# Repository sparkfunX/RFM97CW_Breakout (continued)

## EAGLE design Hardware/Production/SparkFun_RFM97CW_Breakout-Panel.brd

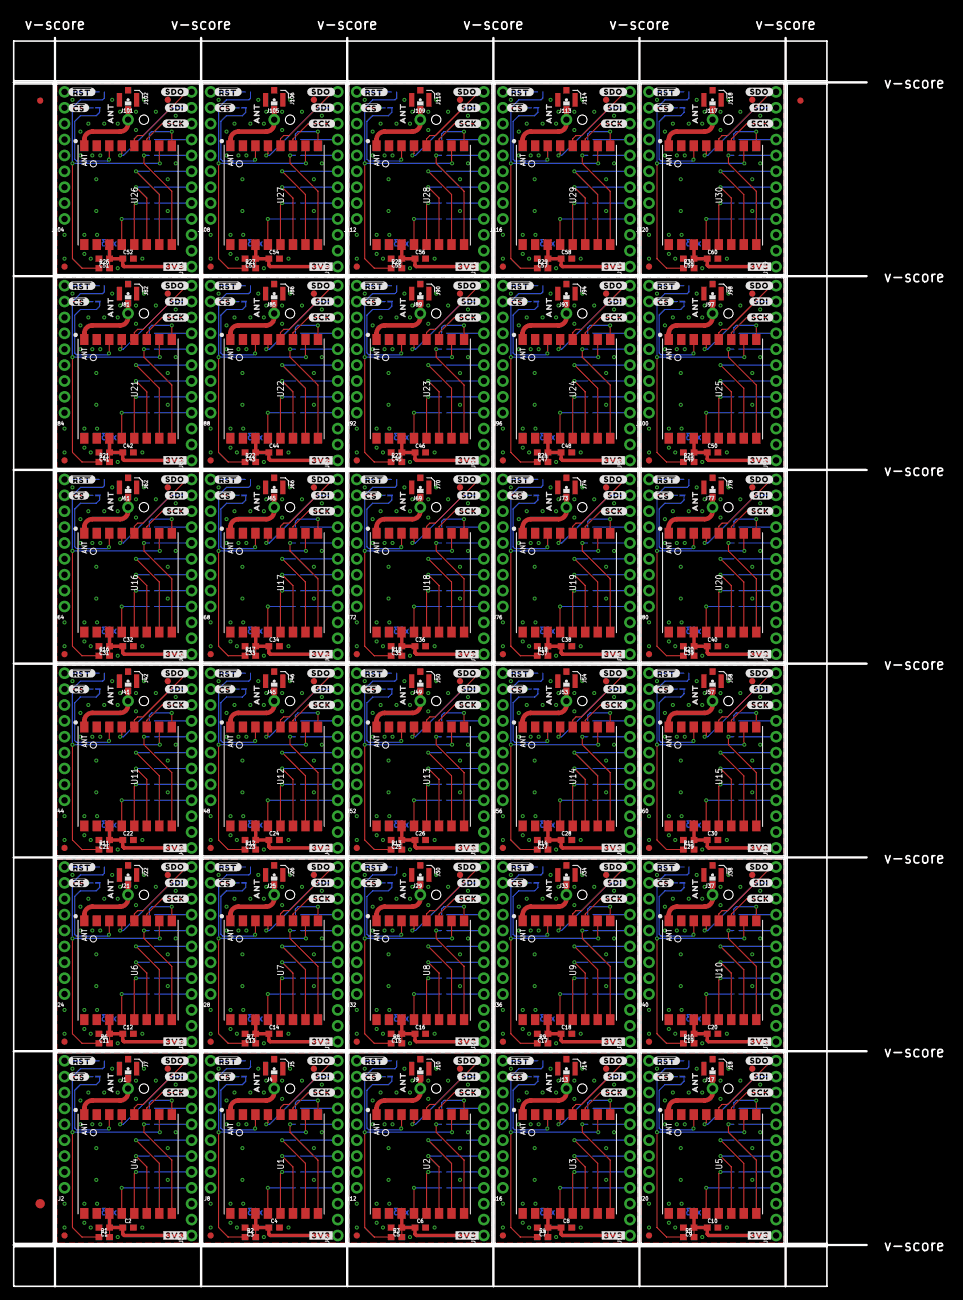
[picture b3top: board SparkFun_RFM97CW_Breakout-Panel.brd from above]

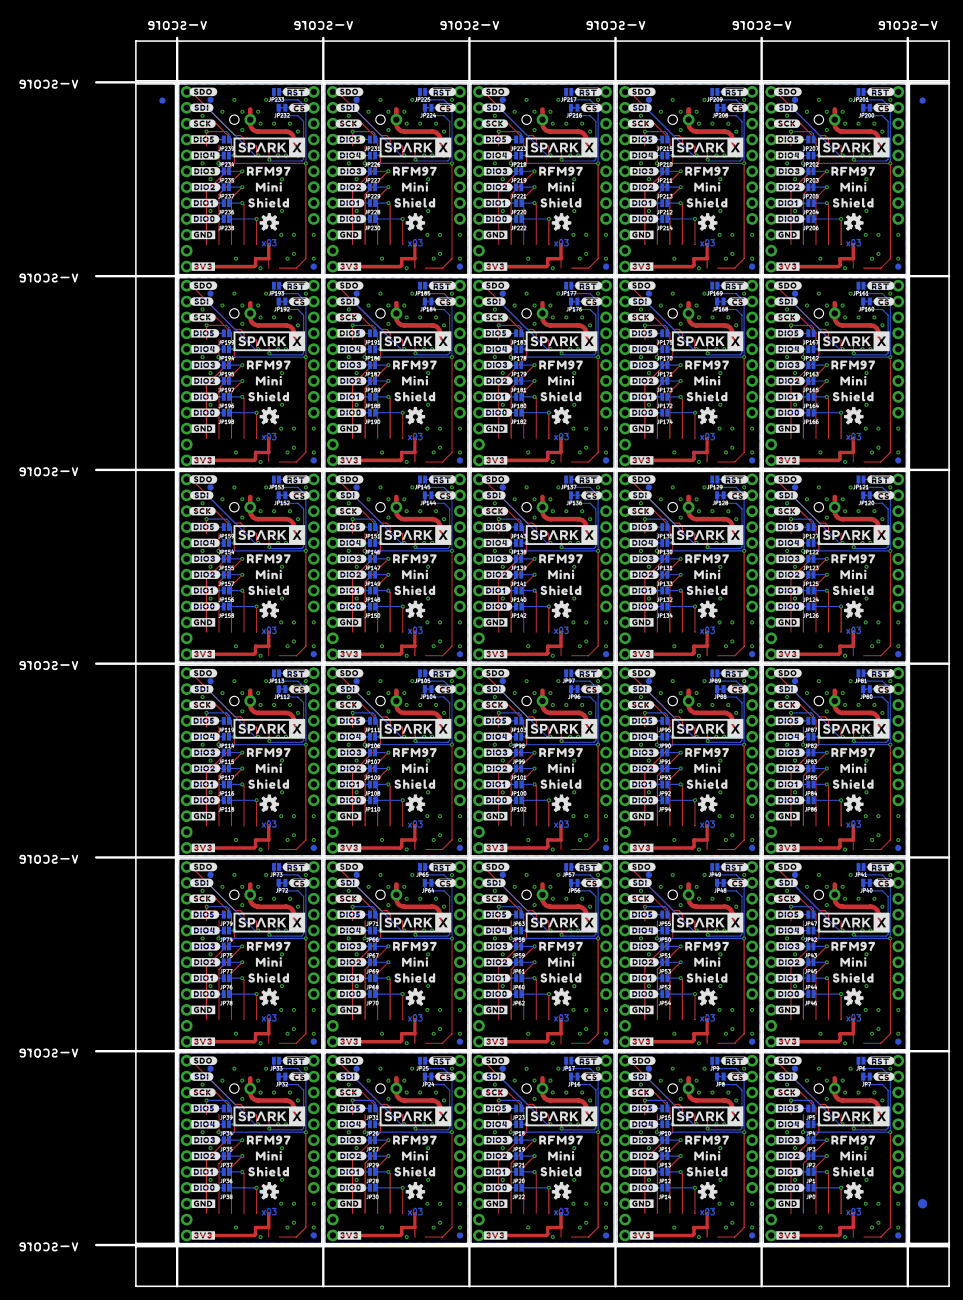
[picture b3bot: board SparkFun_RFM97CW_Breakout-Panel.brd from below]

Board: 2 copper layers, 149.6 x 203.5 mm, 1356 parts (843 on the bottom side), 660 nets.

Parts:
C1, C3, C5, C7, C9, C11, C13, C15, C17, C19, C21, C23, C25, C27, C29, C31, C33, C35, C37, C39, C41, C43, C45, C47, C49, C51, C53, C55, C57, C59: 10uF; 0603
C2, C4, C6, C8, C10, C12, C14, C16, C18, C20, C22, C24, C26, C28, C30, C32, C34, C36, C38, C40, C42, C44, C46, C48, C50, C52, C54, C56, C58, C60: 0.1uF; 0603
E$1, E$2, E$3, E$4: FIDUCIAL-1X2
E$5, E$6: FIDUCIAL-1.5X3
FID1, FID2, FID3, FID4, FID5, FID6, FID7, FID8, FID9, FID10, FID11, FID12, FID13, FID14, FID15, FID16, FID17, FID18, FID19, FID20, FID21, FID22, FID23, FID24, FID25, FID26, FID27, FID28, FID29, FID30, FID31, FID32, FID33, FID34, FID35, FID36, FID37, FID38, FID39, FID40, FID41, FID42, FID43, FID44, FID45, FID46, FID47, FID48, FID49, FID50, FID51, FID52, FID53, FID54, FID55, FID56, FID57, FID58, FID59, FID60, FID61, FID62, FID63, FID64, FID65, FID66, FID67, FID68, FID69, FID70, FID71, FID72, FID73, FID74, FID75, FID76, FID77, FID78, FID79, FID80, FID81, FID82, FID83, FID84, FID85, FID86, FID87, FID88, FID89, FID90, FID91, FID92, FID93, FID94, FID95, FID96, FID97, FID98, FID99, FID100, FID101, FID102, FID103, FID104, FID105, FID106, FID107, FID108, FID109, FID110, FID111, FID112, FID113, FID114, FID115, FID116, FID117, FID118, FID119, FID120: FIDUCIAL1X2; FIDUCIAL-1X2
J1, J4, J9, J13, J17, J21, J25, J29, J33, J37, J41, J45, J49, J53, J57, J61, J65, J69, J73, J77, J81, J85, J89, J93, J97, J101, J105, J109, J113, J117: 1X01_NO_SILK
J2, J8, J12, J16, J20, J24, J28, J32, J36, J40, J44, J48, J52, J56, J60, J64, J68, J72, J76, J80, J84, J88, J92, J96, J100, J104, J108, J112, J116, J120: 1X09_NO_SILK
J3, J6, J11, J15, J19, J23, J27, J31, J35, J39, J43, J47, J51, J55, J59, J63, J67, J71, J75, J79, J83, J87, J91, J95, J99, J103, J107, J111, J115, J119: 1X12_NO_SILK
J5, J7, J10, J14, J18, J22, J26, J30, J34, J38, J42, J46, J50, J54, J58, J62, J66, J70, J74, J78, J82, J86, J90, J94, J98, J102, J106, J110, J114, J118: U.FL
JP0, JP1, JP2, JP3, JP4, JP5, JP6, JP9, JP10, JP11, JP12, JP13, JP14, JP15, JP17, JP18, JP19, JP20, JP21, JP22, JP23, JP25, JP26, JP27, JP28, JP29, JP30, JP31, JP33, JP34, JP35, JP36, JP37, JP38, JP39, JP41, JP42, JP43, JP44, JP45, JP46, JP47, JP49, JP50, JP51, JP52, JP53, JP54, JP55, JP57, JP58, JP59, JP60, JP61, JP62, JP63, JP65, JP66, JP67, JP68, JP69, JP70, JP71, JP73, JP74, JP75, JP76, JP77, JP78, JP79, JP81, JP82, JP83, JP84, JP85, JP86, JP87, JP89, JP90, JP91, JP92, JP93, JP94, JP95, JP97, JP98, JP99, JP100, JP101, JP102, JP103, JP105, JP106, JP107, JP108, JP109, JP110, JP111, JP113, JP114, JP115, JP116, JP117, JP118, JP119, JP121, JP122, JP123, JP124, JP125, JP126, JP127, JP129, JP130, JP131, JP132, JP133, JP134, JP135, JP137, JP138, JP139, JP140, JP141, JP142, JP143, JP145, JP146, JP147, JP148, JP149, JP150, JP151, JP153, JP154, JP155, JP156, JP157, JP158, JP159, JP161, JP162, JP163, JP164, JP165, JP166, JP167, JP169, JP170, JP171, JP172, JP173, JP174, JP175, JP177, JP178, JP179, JP180, JP181, JP182, JP183, JP185, JP186, JP187, JP188, JP189, JP190, JP191, JP193, JP194, JP195, JP196, JP197, JP198, JP199, JP201, JP202, JP203, JP204, JP205, JP206, JP207, JP209, JP210, JP211, JP212, JP213, JP214, JP215, JP217, JP218, JP219, JP220, JP221, JP222, JP223, JP225, JP226, JP227, JP228, JP229, JP230, JP231, JP233, JP234, JP235, JP236, JP237, JP238, JP239: JUMPER-SMT_2_NO_NO-SILK; SMT-JUMPER_2_NO_NO-SILK
JP7, JP8, JP16, JP24, JP32, JP40, JP48, JP56, JP64, JP72, JP80, JP88, JP96, JP104, JP112, JP120, JP128, JP136, JP144, JP152, JP160, JP168, JP176, JP184, JP192, JP200, JP208, JP216, JP224, JP232: JUMPER-SMT_2_NC_TRACE_NO-SILK; SMT-JUMPER_2_NC_TRACE_NO-SILK
LOGO1, LOGO2, LOGO3, LOGO4, LOGO5, LOGO6, LOGO7, LOGO8, LOGO9, LOGO10, LOGO11, LOGO12, LOGO13, LOGO14, LOGO15, LOGO16, LOGO17, LOGO18, LOGO19, LOGO20, LOGO21, LOGO22, LOGO23, LOGO24, LOGO25, LOGO26, LOGO27, LOGO28, LOGO29, LOGO30: OSHW-LOGOS; OSHW-LOGO-S
R1, R2, R3, R4, R5, R6, R7, R8, R9, R10, R11, R12, R13, R14, R15, R16, R17, R18, R19, R20, R21, R22, R23, R24, R25, R26, R27, R28, R29, R30: 10k; 0603
U1, U2, U3, U4, U5, U6, U7, U8, U9, U10, U11, U12, U13, U14, U15, U16, U17, U18, U19, U20, U21, U22, U23, U24, U25, U26, U27, U28, U29, U30: RFM97CW; RFM97
U$1, U$14, U$49, U$73, U$97, U$121, U$145, U$169, U$193, U$217, U$241, U$265, U$289, U$313, U$337, U$361, U$385, U$409, U$433, U$457, U$481, U$505, U$529, U$553, U$577, U$601, U$625, U$649, U$673, U$697: ANT0
U$2, U$21, U$33, U$34, U$57, U$58, U$81, U$82, U$105, U$106, U$129, U$130, U$153, U$154, U$177, U$178, U$201, U$202, U$225, U$226, U$249, U$250, U$273, U$274, U$297, U$298, U$321, U$322, U$345, U$346, U$369, U$370, U$393, U$394, U$417, U$418, U$441, U$442, U$465, U$466, U$489, U$490, U$513, U$514, U$537, U$538, U$561, U$562, U$585, U$586, U$609, U$610, U$633, U$634, U$657, U$658, U$681, U$682, U$705, U$706: ##CS##2
U$3, U$7, U$16, U$35, U$51, U$59, U$75, U$83, U$99, U$107, U$123, U$131, U$147, U$155, U$171, U$179, U$195, U$203, U$219, U$227, U$243, U$251, U$267, U$275, U$291, U$299, U$315, U$323, U$339, U$347, U$363, U$371, U$387, U$395, U$411, U$419, U$435, U$443, U$459, U$467, U$483, U$491, U$507, U$515, U$531, U$539, U$555, U$563, U$579, U$587, U$603, U$611, U$627, U$635, U$651, U$659, U$675, U$683, U$699, U$707: #SDO#0
U$4, U$6, U$15, U$36, U$50, U$60, U$74, U$84, U$98, U$108, U$122, U$132, U$146, U$156, U$170, U$180, U$194, U$204, U$218, U$228, U$242, U$252, U$266, U$276, U$290, U$300, U$314, U$324, U$338, U$348, U$362, U$372, U$386, U$396, U$410, U$420, U$434, U$444, U$458, U$468, U$482, U$492, U$506, U$516, U$530, U$540, U$554, U$564, U$578, U$588, U$602, U$612, U$626, U$636, U$650, U$660, U$674, U$684, U$698, U$708: #SDI#1
U$5, U$12, U$45, U$46, U$69, U$70, U$93, U$94, U$117, U$118, U$141, U$142, U$165, U$166, U$189, U$190, U$213, U$214, U$237, U$238, U$261, U$262, U$285, U$286, U$309, U$310, U$333, U$334, U$357, U$358, U$381, U$382, U$405, U$406, U$429, U$430, U$453, U$454, U$477, U$478, U$501, U$502, U$525, U$526, U$549, U$550, U$573, U$574, U$597, U$598, U$621, U$622, U$645, U$646, U$669, U$670, U$693, U$694, U$717, U$718: #SCK#0
U$8, U$9, U$18, U$29, U$52, U$53, U$76, U$77, U$100, U$101, U$124, U$125, U$148, U$149, U$172, U$173, U$196, U$197, U$220, U$221, U$244, U$245, U$268, U$269, U$292, U$293, U$316, U$317, U$340, U$341, U$364, U$365, U$388, U$389, U$412, U$413, U$436, U$437, U$460, U$461, U$484, U$485, U$508, U$509, U$532, U$533, U$556, U$557, U$580, U$581, U$604, U$605, U$628, U$629, U$652, U$653, U$676, U$677, U$700, U$701: #3V3#0
U$10, U$30, U$54, U$78, U$102, U$126, U$150, U$174, U$198, U$222, U$246, U$270, U$294, U$318, U$342, U$366, U$390, U$414, U$438, U$462, U$486, U$510, U$534, U$558, U$582, U$606, U$630, U$654, U$678, U$702: #GND#1
U$11, U$48, U$72, U$96, U$120, U$144, U$168, U$192, U$216, U$240, U$264, U$288, U$312, U$336, U$360, U$384, U$408, U$432, U$456, U$480, U$504, U$528, U$552, U$576, U$600, U$624, U$648, U$672, U$696, U$720: MINI0
U$13, U$17, U$38, U$47, U$62, U$71, U$86, U$95, U$110, U$119, U$134, U$143, U$158, U$167, U$182, U$191, U$206, U$215, U$230, U$239, U$254, U$263, U$278, U$287, U$302, U$311, U$326, U$335, U$350, U$359, U$374, U$383, U$398, U$407, U$422, U$431, U$446, U$455, U$470, U$479, U$494, U$503, U$518, U$527, U$542, U$551, U$566, U$575, U$590, U$599, U$614, U$623, U$638, U$647, U$662, U$671, U$686, U$695, U$710, U$719: ##RST##0
U$19, U$31, U$55, U$79, U$103, U$127, U$151, U$175, U$199, U$223, U$247, U$271, U$295, U$319, U$343, U$367, U$391, U$415, U$439, U$463, U$487, U$511, U$535, U$559, U$583, U$607, U$631, U$655, U$679, U$703: RFM970
U$20, U$32, U$56, U$80, U$104, U$128, U$152, U$176, U$200, U$224, U$248, U$272, U$296, U$320, U$344, U$368, U$392, U$416, U$440, U$464, U$488, U$512, U$536, U$560, U$584, U$608, U$632, U$656, U$680, U$704: SHIELD2
U$22, U$37, U$61, U$85, U$109, U$133, U$157, U$181, U$205, U$229, U$253, U$277, U$301, U$325, U$349, U$373, U$397, U$421, U$445, U$469, U$493, U$517, U$541, U$565, U$589, U$613, U$637, U$661, U$685, U$709: SPARKX-LOGO5; SPARKX-LARGE
U$23, U$39, U$63, U$87, U$111, U$135, U$159, U$183, U$207, U$231, U$255, U$279, U$303, U$327, U$351, U$375, U$399, U$423, U$447, U$471, U$495, U$519, U$543, U$567, U$591, U$615, U$639, U$663, U$687, U$711: #DIO0#0
U$24, U$40, U$64, U$88, U$112, U$136, U$160, U$184, U$208, U$232, U$256, U$280, U$304, U$328, U$352, U$376, U$400, U$424, U$448, U$472, U$496, U$520, U$544, U$568, U$592, U$616, U$640, U$664, U$688, U$712: #DIO1#0
U$25, U$41, U$65, U$89, U$113, U$137, U$161, U$185, U$209, U$233, U$257, U$281, U$305, U$329, U$353, U$377, U$401, U$425, U$449, U$473, U$497, U$521, U$545, U$569, U$593, U$617, U$641, U$665, U$689, U$713: #DIO2#0
U$26, U$42, U$66, U$90, U$114, U$138, U$162, U$186, U$210, U$234, U$258, U$282, U$306, U$330, U$354, U$378, U$402, U$426, U$450, U$474, U$498, U$522, U$546, U$570, U$594, U$618, U$642, U$666, U$690, U$714: #DIO3#0
U$27, U$43, U$67, U$91, U$115, U$139, U$163, U$187, U$211, U$235, U$259, U$283, U$307, U$331, U$355, U$379, U$403, U$427, U$451, U$475, U$499, U$523, U$547, U$571, U$595, U$619, U$643, U$667, U$691, U$715: #DIO4#0
U$28, U$44, U$68, U$92, U$116, U$140, U$164, U$188, U$212, U$236, U$260, U$284, U$308, U$332, U$356, U$380, U$404, U$428, U$452, U$476, U$500, U$524, U$548, U$572, U$596, U$620, U$644, U$668, U$692, U$716: #DIO5#0

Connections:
3.3V: C1.1, C2.1, J3.1, R1.2, U4.3V3
3.3V1: C3.1, C4.1, J6.1, R2.2, U1.3V3
3.3V2: C5.1, C6.1, J11.1, R3.2, U2.3V3
3.3V3: C7.1, C8.1, J15.1, R4.2, U3.3V3
3.3V4: C9.1, C10.1, J19.1, R5.2, U5.3V3
3.3V5: C11.1, C12.1, J23.1, R6.2, U6.3V3
3.3V6: C13.1, C14.1, J27.1, R7.2, U7.3V3
3.3V7: C15.1, C16.1, J31.1, R8.2, U8.3V3
3.3V8: C17.1, C18.1, J35.1, R9.2, U9.3V3
3.3V9: C19.1, C20.1, J39.1, R10.2, U10.3V3
3.3V10: C21.1, C22.1, J43.1, R11.2, U11.3V3
3.3V11: C23.1, C24.1, J47.1, R12.2, U12.3V3
3.3V12: C25.1, C26.1, J51.1, R13.2, U13.3V3
3.3V13: C27.1, C28.1, J55.1, R14.2, U14.3V3
3.3V14: C29.1, C30.1, J59.1, R15.2, U15.3V3
3.3V15: C31.1, C32.1, J63.1, R16.2, U16.3V3
3.3V16: C33.1, C34.1, J67.1, R17.2, U17.3V3
3.3V17: C35.1, C36.1, J71.1, R18.2, U18.3V3
3.3V18: C37.1, C38.1, J75.1, R19.2, U19.3V3
3.3V19: C39.1, C40.1, J79.1, R20.2, U20.3V3
3.3V20: C41.1, C42.1, J83.1, R21.2, U21.3V3
3.3V21: C43.1, C44.1, J87.1, R22.2, U22.3V3
3.3V22: C45.1, C46.1, J91.1, R23.2, U23.3V3
3.3V23: C47.1, C48.1, J95.1, R24.2, U24.3V3
3.3V24: C49.1, C50.1, J99.1, R25.2, U25.3V3
3.3V25: C51.1, C52.1, J103.1, R26.2, U26.3V3
3.3V26: C53.1, C54.1, J107.1, R27.2, U27.3V3
3.3V27: C55.1, C56.1, J111.1, R28.2, U28.3V3
3.3V28: C57.1, C58.1, J115.1, R29.2, U29.3V3
3.3V29: C59.1, C60.1, J119.1, R30.2, U30.3V3
!CS!: JP7.1, U4.!CS!
!CS!1: JP8.1, U1.!CS!
!CS!2: JP16.1, U2.!CS!
!CS!3: JP24.1, U3.!CS!
!CS!4: JP32.1, U5.!CS!
!CS!5: JP40.1, U6.!CS!
!CS!6: JP48.1, U7.!CS!
!CS!7: JP56.1, U8.!CS!
!CS!8: JP64.1, U9.!CS!
!CS!9: JP72.1, U10.!CS!
!CS!10: JP80.1, U11.!CS!
!CS!11: JP88.1, U12.!CS!
!CS!12: JP96.1, U13.!CS!
!CS!13: JP104.1, U14.!CS!
!CS!14: JP112.1, U15.!CS!
!CS!15: JP120.1, U16.!CS!
!CS!16: JP128.1, U17.!CS!
!CS!17: JP136.1, U18.!CS!
!CS!18: JP144.1, U19.!CS!
!CS!19: JP152.1, U20.!CS!
!CS!20: JP160.1, U21.!CS!
!CS!21: JP168.1, U22.!CS!
!CS!22: JP176.1, U23.!CS!
!CS!23: JP184.1, U24.!CS!
!CS!24: JP192.1, U25.!CS!
!CS!25: JP200.1, U26.!CS!
!CS!26: JP208.1, U27.!CS!
!CS!27: JP216.1, U28.!CS!
!CS!28: JP224.1, U29.!CS!
!CS!29: JP232.1, U30.!CS!
!RST!: JP6.1, R1.1, U4.!RST
!RST!1: JP9.1, R2.1, U1.!RST
!RST!2: JP17.1, R3.1, U2.!RST
!RST!3: JP25.1, R4.1, U3.!RST
!RST!4: JP33.1, R5.1, U5.!RST
!RST!5: JP41.1, R6.1, U6.!RST
!RST!6: JP49.1, R7.1, U7.!RST
!RST!7: JP57.1, R8.1, U8.!RST
!RST!8: JP65.1, R9.1, U9.!RST
!RST!9: JP73.1, R10.1, U10.!RST
!RST!10: JP81.1, R11.1, U11.!RST
!RST!11: JP89.1, R12.1, U12.!RST
!RST!12: JP97.1, R13.1, U13.!RST
!RST!13: JP105.1, R14.1, U14.!RST
!RST!14: JP113.1, R15.1, U15.!RST
!RST!15: JP121.1, R16.1, U16.!RST
!RST!16: JP129.1, R17.1, U17.!RST
!RST!17: JP137.1, R18.1, U18.!RST
!RST!18: JP145.1, R19.1, U19.!RST
!RST!19: JP153.1, R20.1, U20.!RST
!RST!20: JP161.1, R21.1, U21.!RST
!RST!21: JP169.1, R22.1, U22.!RST
!RST!22: JP177.1, R23.1, U23.!RST
!RST!23: JP185.1, R24.1, U24.!RST
!RST!24: JP193.1, R25.1, U25.!RST
!RST!25: JP201.1, R26.1, U26.!RST
!RST!26: JP209.1, R27.1, U27.!RST
!RST!27: JP217.1, R28.1, U28.!RST
!RST!28: JP225.1, R29.1, U29.!RST
!RST!29: JP233.1, R30.1, U30.!RST
ANT: J1.1, J7.FEED, U4.ANT
ANT1: J4.1, J5.FEED, U1.ANT
ANT2: J9.1, J10.FEED, U2.ANT
ANT3: J13.1, J14.FEED, U3.ANT
ANT4: J17.1, J18.FEED, U5.ANT
ANT5: J21.1, J22.FEED, U6.ANT
ANT6: J25.1, J26.FEED, U7.ANT
ANT7: J29.1, J30.FEED, U8.ANT
ANT8: J33.1, J34.FEED, U9.ANT
ANT9: J37.1, J38.FEED, U10.ANT
ANT10: J41.1, J42.FEED, U11.ANT
ANT11: J45.1, J46.FEED, U12.ANT
ANT12: J49.1, J50.FEED, U13.ANT
ANT13: J53.1, J54.FEED, U14.ANT
ANT14: J57.1, J58.FEED, U15.ANT
ANT15: J61.1, J62.FEED, U16.ANT
ANT16: J65.1, J66.FEED, U17.ANT
ANT17: J69.1, J70.FEED, U18.ANT
ANT18: J73.1, J74.FEED, U19.ANT
ANT19: J77.1, J78.FEED, U20.ANT
ANT20: J81.1, J82.FEED, U21.ANT
ANT21: J85.1, J86.FEED, U22.ANT
ANT22: J89.1, J90.FEED, U23.ANT
ANT23: J93.1, J94.FEED, U24.ANT
ANT24: J97.1, J98.FEED, U25.ANT
ANT25: J101.1, J102.FEED, U26.ANT
ANT26: J105.1, J106.FEED, U27.ANT
ANT27: J109.1, J110.FEED, U28.ANT
ANT28: J113.1, J114.FEED, U29.ANT
ANT29: J117.1, J118.FEED, U30.ANT
DIO0: JP0.1, U4.DIO0
DIO1: JP1.1, U4.DIO1
DIO2: JP2.1, U4.DIO2
DIO3: JP3.1, U4.DIO3
DIO4: JP4.1, U4.DIO4
DIO5: JP5.1, U4.DIO5
DIO6: JP14.1, U1.DIO0
DIO7: JP12.1, U1.DIO1
DIO8: JP13.1, U1.DIO2
DIO9: JP11.1, U1.DIO3
DIO10: JP10.1, U1.DIO4
DIO11: JP15.1, U1.DIO5
DIO12: JP22.1, U2.DIO0
DIO13: JP20.1, U2.DIO1
DIO14: JP21.1, U2.DIO2
DIO15: JP19.1, U2.DIO3
DIO16: JP18.1, U2.DIO4
DIO17: JP23.1, U2.DIO5
DIO18: JP30.1, U3.DIO0
DIO19: JP28.1, U3.DIO1
DIO20: JP29.1, U3.DIO2
DIO21: JP27.1, U3.DIO3
DIO22: JP26.1, U3.DIO4
DIO23: JP31.1, U3.DIO5
DIO24: JP38.1, U5.DIO0
DIO25: JP36.1, U5.DIO1
DIO26: JP37.1, U5.DIO2
DIO27: JP35.1, U5.DIO3
DIO28: JP34.1, U5.DIO4
DIO29: JP39.1, U5.DIO5
DIO30: JP46.1, U6.DIO0
DIO31: JP44.1, U6.DIO1
DIO32: JP45.1, U6.DIO2
DIO33: JP43.1, U6.DIO3
DIO34: JP42.1, U6.DIO4
DIO35: JP47.1, U6.DIO5
DIO36: JP54.1, U7.DIO0
DIO37: JP52.1, U7.DIO1
DIO38: JP53.1, U7.DIO2
DIO39: JP51.1, U7.DIO3
DIO40: JP50.1, U7.DIO4
DIO41: JP55.1, U7.DIO5
DIO42: JP62.1, U8.DIO0
DIO43: JP60.1, U8.DIO1
DIO44: JP61.1, U8.DIO2
DIO45: JP59.1, U8.DIO3
DIO46: JP58.1, U8.DIO4
DIO47: JP63.1, U8.DIO5
DIO48: JP70.1, U9.DIO0
DIO49: JP68.1, U9.DIO1
DIO50: JP69.1, U9.DIO2
DIO51: JP67.1, U9.DIO3
DIO52: JP66.1, U9.DIO4
DIO53: JP71.1, U9.DIO5
DIO54: JP78.1, U10.DIO0
DIO55: JP76.1, U10.DIO1
DIO56: JP77.1, U10.DIO2
DIO57: JP75.1, U10.DIO3
DIO58: JP74.1, U10.DIO4
DIO59: JP79.1, U10.DIO5
DIO60: JP86.1, U11.DIO0
DIO61: JP84.1, U11.DIO1
DIO62: JP85.1, U11.DIO2
DIO63: JP83.1, U11.DIO3
DIO64: JP82.1, U11.DIO4
DIO65: JP87.1, U11.DIO5
DIO66: JP94.1, U12.DIO0
DIO67: JP92.1, U12.DIO1
DIO68: JP93.1, U12.DIO2
DIO69: JP91.1, U12.DIO3
DIO70: JP90.1, U12.DIO4
DIO71: JP95.1, U12.DIO5
DIO72: JP102.1, U13.DIO0
DIO73: JP100.1, U13.DIO1
DIO74: JP101.1, U13.DIO2
DIO75: JP99.1, U13.DIO3
DIO76: JP98.1, U13.DIO4
DIO77: JP103.1, U13.DIO5
DIO78: JP110.1, U14.DIO0
DIO79: JP108.1, U14.DIO1
DIO80: JP109.1, U14.DIO2
DIO81: JP107.1, U14.DIO3
DIO82: JP106.1, U14.DIO4
DIO83: JP111.1, U14.DIO5
DIO84: JP118.1, U15.DIO0
DIO85: JP116.1, U15.DIO1
DIO86: JP117.1, U15.DIO2
DIO87: JP115.1, U15.DIO3
DIO88: JP114.1, U15.DIO4
DIO89: JP119.1, U15.DIO5
DIO90: JP126.1, U16.DIO0
DIO91: JP124.1, U16.DIO1
DIO92: JP125.1, U16.DIO2
DIO93: JP123.1, U16.DIO3
DIO94: JP122.1, U16.DIO4
DIO95: JP127.1, U16.DIO5
DIO96: JP134.1, U17.DIO0
DIO97: JP132.1, U17.DIO1
DIO98: JP133.1, U17.DIO2
DIO99: JP131.1, U17.DIO3
DIO100: JP130.1, U17.DIO4
DIO101: JP135.1, U17.DIO5
DIO102: JP142.1, U18.DIO0
DIO103: JP140.1, U18.DIO1
DIO104: JP141.1, U18.DIO2
DIO105: JP139.1, U18.DIO3
DIO106: JP138.1, U18.DIO4
DIO107: JP143.1, U18.DIO5
DIO108: JP150.1, U19.DIO0
DIO109: JP148.1, U19.DIO1
DIO110: JP149.1, U19.DIO2
DIO111: JP147.1, U19.DIO3
DIO112: JP146.1, U19.DIO4
DIO113: JP151.1, U19.DIO5
DIO114: JP158.1, U20.DIO0
DIO115: JP156.1, U20.DIO1
DIO116: JP157.1, U20.DIO2
DIO117: JP155.1, U20.DIO3
DIO118: JP154.1, U20.DIO4
DIO119: JP159.1, U20.DIO5
DIO120: JP166.1, U21.DIO0
DIO121: JP164.1, U21.DIO1
DIO122: JP165.1, U21.DIO2
DIO123: JP163.1, U21.DIO3
DIO124: JP162.1, U21.DIO4
DIO125: JP167.1, U21.DIO5
DIO126: JP174.1, U22.DIO0
DIO127: JP172.1, U22.DIO1
DIO128: JP173.1, U22.DIO2
DIO129: JP171.1, U22.DIO3
DIO130: JP170.1, U22.DIO4
DIO131: JP175.1, U22.DIO5
DIO132: JP182.1, U23.DIO0
DIO133: JP180.1, U23.DIO1
DIO134: JP181.1, U23.DIO2
DIO135: JP179.1, U23.DIO3
DIO136: JP178.1, U23.DIO4
DIO137: JP183.1, U23.DIO5
DIO138: JP190.1, U24.DIO0
DIO139: JP188.1, U24.DIO1
DIO140: JP189.1, U24.DIO2
DIO141: JP187.1, U24.DIO3
DIO142: JP186.1, U24.DIO4
DIO143: JP191.1, U24.DIO5
DIO144: JP198.1, U25.DIO0
DIO145: JP196.1, U25.DIO1
DIO146: JP197.1, U25.DIO2
DIO147: JP195.1, U25.DIO3
DIO148: JP194.1, U25.DIO4
DIO149: JP199.1, U25.DIO5
DIO150: JP206.1, U26.DIO0
DIO151: JP204.1, U26.DIO1
DIO152: JP205.1, U26.DIO2
DIO153: JP203.1, U26.DIO3
DIO154: JP202.1, U26.DIO4
DIO155: JP207.1, U26.DIO5
DIO156: JP214.1, U27.DIO0
DIO157: JP212.1, U27.DIO1
DIO158: JP213.1, U27.DIO2
DIO159: JP211.1, U27.DIO3
DIO160: JP210.1, U27.DIO4
DIO161: JP215.1, U27.DIO5
DIO162: JP222.1, U28.DIO0
DIO163: JP220.1, U28.DIO1
DIO164: JP221.1, U28.DIO2
DIO165: JP219.1, U28.DIO3
DIO166: JP218.1, U28.DIO4
DIO167: JP223.1, U28.DIO5
DIO168: JP230.1, U29.DIO0
DIO169: JP228.1, U29.DIO1
DIO170: JP229.1, U29.DIO2
DIO171: JP227.1, U29.DIO3
DIO172: JP226.1, U29.DIO4
DIO173: JP231.1, U29.DIO5
DIO174: JP238.1, U30.DIO0
DIO175: JP236.1, U30.DIO1
DIO176: JP237.1, U30.DIO2
DIO177: JP235.1, U30.DIO3
DIO178: JP234.1, U30.DIO4
DIO179: JP239.1, U30.DIO5
GND: C1.2, C2.2, J3.3, J7.1, J7.2, U4.GND, U4.GND@1, U4.GND@2
GND1: C3.2, C4.2, J5.1, J5.2, J6.3, U1.GND, U1.GND@1, U1.GND@2
GND2: C5.2, C6.2, J10.1, J10.2, J11.3, U2.GND, U2.GND@1, U2.GND@2
GND3: C7.2, C8.2, J14.1, J14.2, J15.3, U3.GND, U3.GND@1, U3.GND@2
GND4: C9.2, C10.2, J18.1, J18.2, J19.3, U5.GND, U5.GND@1, U5.GND@2
GND5: C11.2, C12.2, J22.1, J22.2, J23.3, U6.GND, U6.GND@1, U6.GND@2
GND6: C13.2, C14.2, J26.1, J26.2, J27.3, U7.GND, U7.GND@1, U7.GND@2
GND7: C15.2, C16.2, J30.1, J30.2, J31.3, U8.GND, U8.GND@1, U8.GND@2
GND8: C17.2, C18.2, J34.1, J34.2, J35.3, U9.GND, U9.GND@1, U9.GND@2
GND9: C19.2, C20.2, J38.1, J38.2, J39.3, U10.GND, U10.GND@1, U10.GND@2
GND10: C21.2, C22.2, J42.1, J42.2, J43.3, U11.GND, U11.GND@1, U11.GND@2
GND11: C23.2, C24.2, J46.1, J46.2, J47.3, U12.GND, U12.GND@1, U12.GND@2
GND12: C25.2, C26.2, J50.1, J50.2, J51.3, U13.GND, U13.GND@1, U13.GND@2
GND13: C27.2, C28.2, J54.1, J54.2, J55.3, U14.GND, U14.GND@1, U14.GND@2
GND14: C29.2, C30.2, J58.1, J58.2, J59.3, U15.GND, U15.GND@1, U15.GND@2
GND15: C31.2, C32.2, J62.1, J62.2, J63.3, U16.GND, U16.GND@1, U16.GND@2
GND16: C33.2, C34.2, J66.1, J66.2, J67.3, U17.GND, U17.GND@1, U17.GND@2
GND17: C35.2, C36.2, J70.1, J70.2, J71.3, U18.GND, U18.GND@1, U18.GND@2
GND18: C37.2, C38.2, J74.1, J74.2, J75.3, U19.GND, U19.GND@1, U19.GND@2
GND19: C39.2, C40.2, J78.1, J78.2, J79.3, U20.GND, U20.GND@1, U20.GND@2
GND20: C41.2, C42.2, J82.1, J82.2, J83.3, U21.GND, U21.GND@1, U21.GND@2
GND21: C43.2, C44.2, J86.1, J86.2, J87.3, U22.GND, U22.GND@1, U22.GND@2
GND22: C45.2, C46.2, J90.1, J90.2, J91.3, U23.GND, U23.GND@1, U23.GND@2
GND23: C47.2, C48.2, J94.1, J94.2, J95.3, U24.GND, U24.GND@1, U24.GND@2
GND24: C49.2, C50.2, J98.1, J98.2, J99.3, U25.GND, U25.GND@1, U25.GND@2
GND25: C51.2, C52.2, J102.1, J102.2, J103.3, U26.GND, U26.GND@1, U26.GND@2
GND26: C53.2, C54.2, J106.1, J106.2, J107.3, U27.GND, U27.GND@1, U27.GND@2
GND27: C55.2, C56.2, J110.1, J110.2, J111.3, U28.GND, U28.GND@1, U28.GND@2
GND28: C57.2, C58.2, J114.1, J114.2, J115.3, U29.GND, U29.GND@1, U29.GND@2
GND29: C59.2, C60.2, J118.1, J118.2, J119.3, U30.GND, U30.GND@1, U30.GND@2
unnamed: J3.6, JP2.2
unnamed: J2.9, JP6.2
unnamed: J2.8, JP7.2
unnamed: J3.5, JP1.2
unnamed: J3.4, JP0.2
unnamed: J3.7, JP3.2
unnamed: J3.8, JP4.2
unnamed: J3.9, JP5.2
unnamed: J6.7, JP11.2
unnamed: J6.8, JP10.2
unnamed: J6.6, JP13.2
unnamed: J6.5, JP12.2
unnamed: J6.4, JP14.2
unnamed: J6.9, JP15.2
unnamed: J8.9, JP9.2
unnamed: J8.8, JP8.2
unnamed: J11.7, JP19.2
unnamed: J11.8, JP18.2
unnamed: J11.6, JP21.2
unnamed: J11.5, JP20.2
unnamed: J11.4, JP22.2
unnamed: J11.9, JP23.2
unnamed: J12.9, JP17.2
unnamed: J12.8, JP16.2
unnamed: J15.7, JP27.2
unnamed: J15.8, JP26.2
unnamed: J15.6, JP29.2
unnamed: J15.5, JP28.2
unnamed: J15.4, JP30.2
unnamed: J15.9, JP31.2
unnamed: J16.9, JP25.2
unnamed: J16.8, JP24.2
unnamed: J19.7, JP35.2
unnamed: J19.8, JP34.2
unnamed: J19.6, JP37.2
unnamed: J19.5, JP36.2
unnamed: J19.4, JP38.2
unnamed: J19.9, JP39.2
unnamed: J20.9, JP33.2
unnamed: J20.8, JP32.2
unnamed: J23.7, JP43.2
unnamed: J23.8, JP42.2
unnamed: J23.6, JP45.2
unnamed: J23.5, JP44.2
unnamed: J23.4, JP46.2
unnamed: J23.9, JP47.2
unnamed: J24.9, JP41.2
unnamed: J24.8, JP40.2
unnamed: J27.7, JP51.2
unnamed: J27.8, JP50.2
unnamed: J27.6, JP53.2
unnamed: J27.5, JP52.2
unnamed: J27.4, JP54.2
unnamed: J27.9, JP55.2
unnamed: J28.9, JP49.2
unnamed: J28.8, JP48.2
unnamed: J31.7, JP59.2
unnamed: J31.8, JP58.2
unnamed: J31.6, JP61.2
unnamed: J31.5, JP60.2
unnamed: J31.4, JP62.2
unnamed: J31.9, JP63.2
unnamed: J32.9, JP57.2
unnamed: J32.8, JP56.2
unnamed: J35.7, JP67.2
unnamed: J35.8, JP66.2
unnamed: J35.6, JP69.2
unnamed: J35.5, JP68.2
unnamed: J35.4, JP70.2
unnamed: J35.9, JP71.2
unnamed: J36.9, JP65.2
unnamed: J36.8, JP64.2
unnamed: J39.7, JP75.2
unnamed: J39.8, JP74.2
unnamed: J39.6, JP77.2
unnamed: J39.5, JP76.2
unnamed: J39.4, JP78.2
unnamed: J39.9, JP79.2
unnamed: J40.9, JP73.2
unnamed: J40.8, JP72.2
unnamed: J43.7, JP83.2
unnamed: J43.8, JP82.2
unnamed: J43.6, JP85.2
unnamed: J43.5, JP84.2
unnamed: J43.4, JP86.2
unnamed: J43.9, JP87.2
unnamed: J44.9, JP81.2
unnamed: J44.8, JP80.2
unnamed: J47.7, JP91.2
unnamed: J47.8, JP90.2
unnamed: J47.6, JP93.2
unnamed: J47.5, JP92.2
unnamed: J47.4, JP94.2
unnamed: J47.9, JP95.2
unnamed: J48.9, JP89.2
unnamed: J48.8, JP88.2
unnamed: J51.7, JP99.2
unnamed: J51.8, JP98.2
unnamed: J51.6, JP101.2
unnamed: J51.5, JP100.2
unnamed: J51.4, JP102.2
unnamed: J51.9, JP103.2
unnamed: J52.9, JP97.2
unnamed: J52.8, JP96.2
unnamed: J55.7, JP107.2
unnamed: J55.8, JP106.2
unnamed: J55.6, JP109.2
unnamed: J55.5, JP108.2
unnamed: J55.4, JP110.2
unnamed: J55.9, JP111.2
unnamed: J56.9, JP105.2
unnamed: J56.8, JP104.2
unnamed: J59.7, JP115.2
unnamed: J59.8, JP114.2
unnamed: J59.6, JP117.2
unnamed: J59.5, JP116.2
unnamed: J59.4, JP118.2
unnamed: J59.9, JP119.2
unnamed: J60.9, JP113.2
unnamed: J60.8, JP112.2
unnamed: J63.7, JP123.2
unnamed: J63.8, JP122.2
unnamed: J63.6, JP125.2
unnamed: J63.5, JP124.2
unnamed: J63.4, JP126.2
unnamed: J63.9, JP127.2
unnamed: J64.9, JP121.2
unnamed: J64.8, JP120.2
unnamed: J67.7, JP131.2
unnamed: J67.8, JP130.2
unnamed: J67.6, JP133.2
unnamed: J67.5, JP132.2
unnamed: J67.4, JP134.2
unnamed: J67.9, JP135.2
unnamed: J68.9, JP129.2
unnamed: J68.8, JP128.2
unnamed: J71.7, JP139.2
unnamed: J71.8, JP138.2
unnamed: J71.6, JP141.2
unnamed: J71.5, JP140.2
unnamed: J71.4, JP142.2
unnamed: J71.9, JP143.2
unnamed: J72.9, JP137.2
unnamed: J72.8, JP136.2
unnamed: J75.7, JP147.2
unnamed: J75.8, JP146.2
unnamed: J75.6, JP149.2
unnamed: J75.5, JP148.2
unnamed: J75.4, JP150.2
unnamed: J75.9, JP151.2
unnamed: J76.9, JP145.2
unnamed: J76.8, JP144.2
unnamed: J79.7, JP155.2
unnamed: J79.8, JP154.2
unnamed: J79.6, JP157.2
unnamed: J79.5, JP156.2
unnamed: J79.4, JP158.2
unnamed: J79.9, JP159.2
unnamed: J80.9, JP153.2
unnamed: J80.8, JP152.2
unnamed: J83.7, JP163.2
unnamed: J83.8, JP162.2
unnamed: J83.6, JP165.2
unnamed: J83.5, JP164.2
unnamed: J83.4, JP166.2
unnamed: J83.9, JP167.2
unnamed: J84.9, JP161.2
unnamed: J84.8, JP160.2
unnamed: J87.7, JP171.2
unnamed: J87.8, JP170.2
unnamed: J87.6, JP173.2
unnamed: J87.5, JP172.2
unnamed: J87.4, JP174.2
unnamed: J87.9, JP175.2
unnamed: J88.9, JP169.2
unnamed: J88.8, JP168.2
unnamed: J91.7, JP179.2
unnamed: J91.8, JP178.2
unnamed: J91.6, JP181.2
unnamed: J91.5, JP180.2
unnamed: J91.4, JP182.2
unnamed: J91.9, JP183.2
unnamed: J92.9, JP177.2
unnamed: J92.8, JP176.2
unnamed: J95.7, JP187.2
unnamed: J95.8, JP186.2
unnamed: J95.6, JP189.2
unnamed: J95.5, JP188.2
unnamed: J95.4, JP190.2
unnamed: J95.9, JP191.2
unnamed: J96.9, JP185.2
unnamed: J96.8, JP184.2
unnamed: J99.7, JP195.2
unnamed: J99.8, JP194.2
unnamed: J99.6, JP197.2
unnamed: J99.5, JP196.2
unnamed: J99.4, JP198.2
unnamed: J99.9, JP199.2
unnamed: J100.9, JP193.2
unnamed: J100.8, JP192.2
unnamed: J103.7, JP203.2
unnamed: J103.8, JP202.2
unnamed: J103.6, JP205.2
unnamed: J103.5, JP204.2
unnamed: J103.4, JP206.2
unnamed: J103.9, JP207.2
unnamed: J104.9, JP201.2
unnamed: J104.8, JP200.2
unnamed: J107.7, JP211.2
unnamed: J107.8, JP210.2
unnamed: J107.6, JP213.2
unnamed: J107.5, JP212.2
unnamed: J107.4, JP214.2
unnamed: J107.9, JP215.2
unnamed: J108.9, JP209.2
unnamed: J108.8, JP208.2
unnamed: J111.7, JP219.2
unnamed: J111.8, JP218.2
unnamed: J111.6, JP221.2
unnamed: J111.5, JP220.2
unnamed: J111.4, JP222.2
unnamed: J111.9, JP223.2
unnamed: J112.9, JP217.2
unnamed: J112.8, JP216.2
unnamed: J115.7, JP227.2
unnamed: J115.8, JP226.2
unnamed: J115.6, JP229.2
unnamed: J115.5, JP228.2
unnamed: J115.4, JP230.2
unnamed: J115.9, JP231.2
unnamed: J116.9, JP225.2
unnamed: J116.8, JP224.2
unnamed: J119.7, JP235.2
unnamed: J119.8, JP234.2
unnamed: J119.6, JP237.2
unnamed: J119.5, JP236.2
unnamed: J119.4, JP238.2
unnamed: J119.9, JP239.2
unnamed: J120.9, JP233.2
unnamed: J120.8, JP232.2
SCK: J3.10, U4.SCK
SCK1: J6.10, U1.SCK
SCK2: J11.10, U2.SCK
SCK3: J15.10, U3.SCK
SCK4: J19.10, U5.SCK
SCK5: J23.10, U6.SCK
SCK6: J27.10, U7.SCK
SCK7: J31.10, U8.SCK
SCK8: J35.10, U9.SCK
SCK9: J39.10, U10.SCK
SCK10: J43.10, U11.SCK
SCK11: J47.10, U12.SCK
SCK12: J51.10, U13.SCK
SCK13: J55.10, U14.SCK
SCK14: J59.10, U15.SCK
SCK15: J63.10, U16.SCK
SCK16: J67.10, U17.SCK
SCK17: J71.10, U18.SCK
SCK18: J75.10, U19.SCK
SCK19: J79.10, U20.SCK
SCK20: J83.10, U21.SCK
SCK21: J87.10, U22.SCK
SCK22: J91.10, U23.SCK
SCK23: J95.10, U24.SCK
SCK24: J99.10, U25.SCK
SCK25: J103.10, U26.SCK
SCK26: J107.10, U27.SCK
SCK27: J111.10, U28.SCK
SCK28: J115.10, U29.SCK
SCK29: J119.10, U30.SCK
SDI: J3.11, U4.SDI
SDI1: J6.11, U1.SDI
SDI2: J11.11, U2.SDI
SDI3: J15.11, U3.SDI
SDI4: J19.11, U5.SDI
SDI5: J23.11, U6.SDI
SDI6: J27.11, U7.SDI
SDI7: J31.11, U8.SDI
SDI8: J35.11, U9.SDI
SDI9: J39.11, U10.SDI
SDI10: J43.11, U11.SDI
SDI11: J47.11, U12.SDI
SDI12: J51.11, U13.SDI
SDI13: J55.11, U14.SDI
SDI14: J59.11, U15.SDI
SDI15: J63.11, U16.SDI
SDI16: J67.11, U17.SDI
SDI17: J71.11, U18.SDI
SDI18: J75.11, U19.SDI
SDI19: J79.11, U20.SDI
SDI20: J83.11, U21.SDI
SDI21: J87.11, U22.SDI
SDI22: J91.11, U23.SDI
SDI23: J95.11, U24.SDI
SDI24: J99.11, U25.SDI
SDI25: J103.11, U26.SDI
SDI26: J107.11, U27.SDI
SDI27: J111.11, U28.SDI
SDI28: J115.11, U29.SDI
SDI29: J119.11, U30.SDI
SDO: J3.12, U4.SDO
SDO1: J6.12, U1.SDO
SDO2: J11.12, U2.SDO
SDO3: J15.12, U3.SDO
SDO4: J19.12, U5.SDO
SDO5: J23.12, U6.SDO
SDO6: J27.12, U7.SDO
SDO7: J31.12, U8.SDO
SDO8: J35.12, U9.SDO
SDO9: J39.12, U10.SDO
SDO10: J43.12, U11.SDO
SDO11: J47.12, U12.SDO
SDO12: J51.12, U13.SDO
SDO13: J55.12, U14.SDO
SDO14: J59.12, U15.SDO
SDO15: J63.12, U16.SDO
SDO16: J67.12, U17.SDO
SDO17: J71.12, U18.SDO
SDO18: J75.12, U19.SDO
SDO19: J79.12, U20.SDO
SDO20: J83.12, U21.SDO
SDO21: J87.12, U22.SDO
SDO22: J91.12, U23.SDO
SDO23: J95.12, U24.SDO
SDO24: J99.12, U25.SDO
SDO25: J103.12, U26.SDO
SDO26: J107.12, U27.SDO
SDO27: J111.12, U28.SDO
SDO28: J115.12, U29.SDO
SDO29: J119.12, U30.SDO

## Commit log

2021-07-09 Add datasheet. Organize repo.
2021-07-12 Add extra documents
2021-07-12 Add x02 hardware files
2021-07-21 Adding panel for x02
2021-09-09 Add example sketches. Move silk indicator to match dimple on RF shield. Create x03 panels.
2021-09-22 Add readme and license
